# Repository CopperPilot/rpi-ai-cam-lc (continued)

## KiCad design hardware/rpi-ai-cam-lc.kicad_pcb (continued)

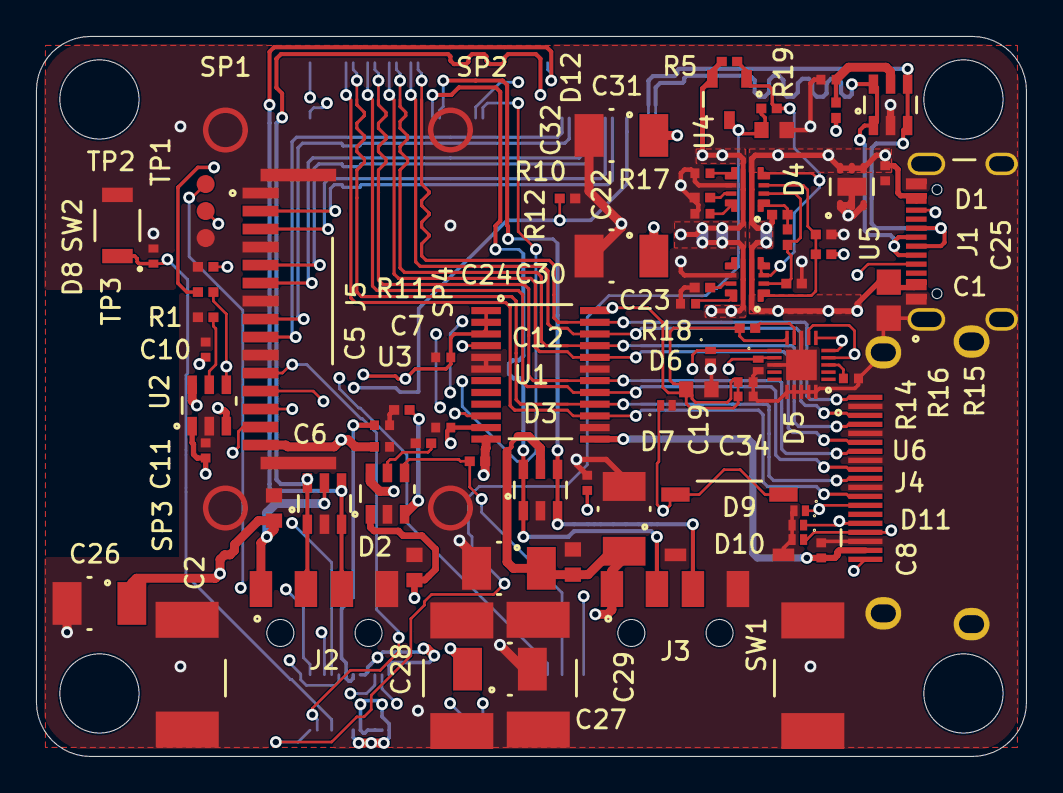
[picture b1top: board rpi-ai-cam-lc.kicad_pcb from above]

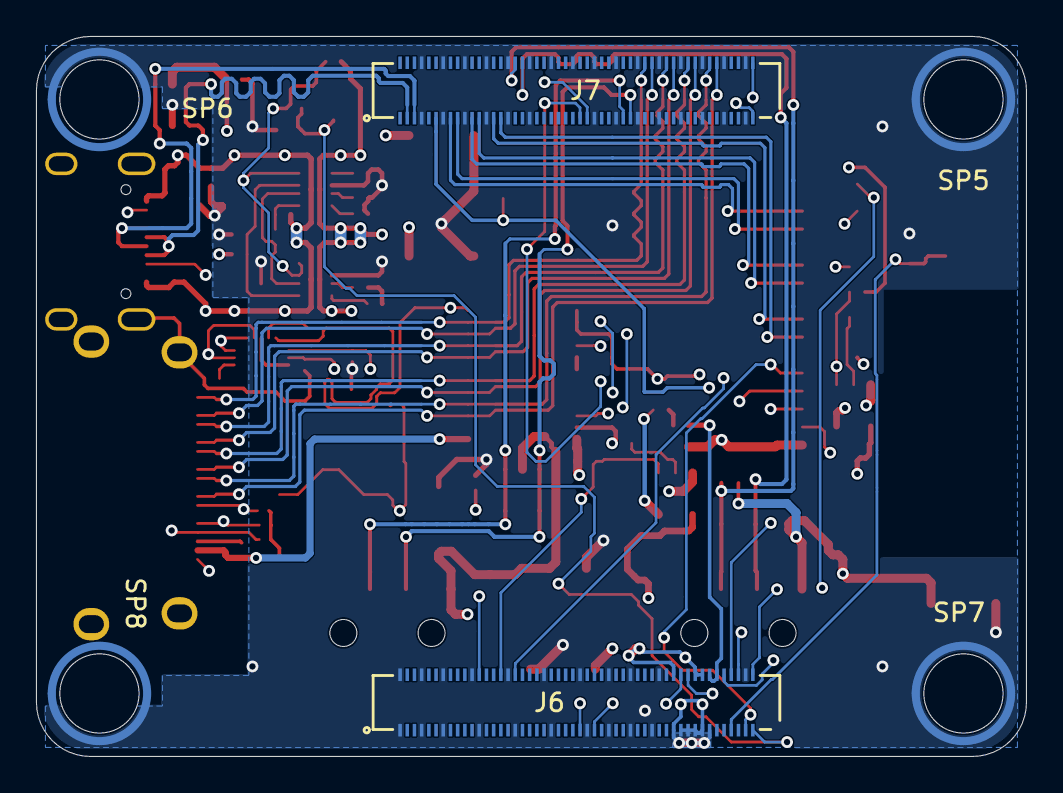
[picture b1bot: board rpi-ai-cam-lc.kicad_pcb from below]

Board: 6 copper layers, 55.0 x 40.0 mm, 88 parts (6 on the bottom side), 64 nets.

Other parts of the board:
H1, H2, H3, H4: MountingHole; MountingHole_4.4mm

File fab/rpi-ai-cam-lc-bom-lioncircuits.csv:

S.No,Manufacturing Part No,Designator,Quantity,Description (VALUE),Package (Case),Top/Bottom,Points (No. of Pins),Comments
1,CL21B225KBYNNWE,C1,1,"2.2uF 50V X7R 0805 MLCC on VBUS_IN (50V >= 1.79x D4 28.0V max clamp, unswitched cSink 2.3uF <= 10uF)",C0805,Top,2,Manufacturer: Samsung Electro-Mechanics
2,CL10A226MO7JZNC,"C2, C3, C19",3,"22uF 16V/10V X5R 0603 MLCC (Samsung CL10A226MO7JZNC / CL10A226MP8NUNE, J5 +3V3 camera bulk decoupling)",C0603,Top,2,Manufacturer: Samsung Electro-Mechanics
3,GRM155R71H104KE14D,"C4, C5, C6, C7, C20, C21, C25, C33",8,100nF 50V X7R 0402 MLCC,C0402,Top,2,Manufacturer: Murata
4,GRM155R61E105KE11J,"C8, C10, C11, C12, C34",5,1uF 25V X5R 0402 MLCC (U3 +5V input bypass),C0402,Top,2,Manufacturer: Murata
5,GRM188Z71E225KE43D,"C9, C32",2,"2.2uF 25V X7R 0603 RC blanking filter capacitor on PMIC_ENABLE (C_eff>=1.68uF at 5V, tau_fall>=10.7ms > 3.94ms t_ITIMER, tau_rise=2.42ms via R5+D12)",C0603,Top,2,Manufacturer: Murata
6,GRM155R71H472KA01D,"C22, C23, C24",3,"4.7nF 50V X7R 0402 dV/dt soft-start capacitor on U4 (SR=0.43V/ms, tR=11.7ms)",C0402,Top,2,Manufacturer: Murata
7,T520B107M010ATE070,"C26, C27, C28, C29, C30, C31",6,100uF 10V 70mOhm KO-CAP polymer tantalum bulk capacitor on J2 USB0_VBUS (1 of 2; 207.5uF effective with C27+C2 >= 120uF USB 2.0 C_PB),CAP-SMD_L3.5-W2.8,Top,2,Manufacturer: Kemet
8,USBLC6-2SC6,"D1, D2, D3",3,USBLC6-2SC6 - USB 2.0 ESD protection array,SOT-23-6_L2.9-W1.6-P0.95-LS2.8-BL,Top,6,Manufacturer: STMicroelectronics
9,TVS2200DRVR,D4,1,"TVS2200DRVR - 22V flat-clamp unidirectional surge TVS on J1 VBUS_IN (VRWM=22V, VBR=24.6-27.6V, VC=27.2V typ/27.7V max at 24A & 27.6V typ/28.0V max at 40A 8/20us <= 28V abs max, VF=-0.5V typ)",WSON-6_L2.0-W2.0-P0.65-TL-EP,Top,7,Manufacturer: Texas Instruments
10,TPD1E05U06DPYR,"D5, D6, D7, D9, D10, D11",6,TPD1E05U06DPYR - 5.5V unidirectional ESD TVS on protected system-side CC2 (downstream of U6 TPD6S300ARUKR 24V OVP FET) to GND,X1SON-2_L1.0-W0.6-P0.65-RD-1,Top,2,Manufacturer: Texas Instruments
11,PESD3V3S1BLYL,D8,1,PESD3V3S1BLYL - 3.3V bidirectional ESD TVS on SW2 nRPIBOOT,DFN1006-2L-BI,Top,2,Manufacturer: Nexperia
12,BAT54S,D12,1,"BAT54S - Dual series 30V 200mA Schottky diode (1->3 fast charge VBUS_AUXOFF->PMIC_ENABLE, 3->2 fast rail-collapse discharge PMIC_ENABLE->+5V)",SOT-23_L2.9-W1.3-P1.90-LS2.4-BR,Top,3,Manufacturer: Rectron
13,USB4105GFA,J1,1,USB4105-GF-A - GCT 16-pin USB 2.0 Type-C horizontal SMT receptacle,TYPE-C-SMD_SBC-160S1A-20-S412,Top,22,Manufacturer: GCT
14,629104190121,"J2, J3",2,629104190121 - Wurth WR-COM USB 2.0 Type-A horizontal SMT receptacle,USB-A-SMD_629104190121,Top,10,Manufacturer: Wurth Elektronik
15,10029449-111RLF,J4,1,10029449-111RLF - Amphenol full-size HDMI Type-A right-angle SMT receptacle,HDMI-SMD_10029449-001RLF,Top,23,Manufacturer: Amphenol ICC
16,SFW15R-1STE1LF,J5,1,SFW15R-1STE1LF - Amphenol 15-pin 1.0 mm right-angle bottom-contact ZIF FFC socket,CONN-SMD_15P-P0.50_SFW15R-1STE1LF,Top,17,Manufacturer: Amphenol Communications Solutions
17,10164227-1001A1RLF,"J6, J7",2,"10164227-1001A1RLF - Amphenol 100-pin 0.4 mm pitch mezzanine receptacle, 1.5 mm stack height (GPIO/Power pins 1-100 at B.Cu 25.0, 37.0, rot=180)",CONN-SMD_100P-P0.40_10164227-1001A1RLF,Bottom,100,Manufacturer: Amphenol Communications Solutions
18,RC0402FR-0743KL,"R1, R2, R16",3,"43k 1% 0402 bottom divider to GND on U5 EN/UVLO (with R15=100k sets UVLO_R=3.99V, UVLO_F=3.66V)",R0402,Top,2,Manufacturer: Yageo
19,RC0402FR-071K33L,"R5, R17, R18",3,"1.33k 1% 0402 current limit resistor for U4 (ILIM(typ)=2.50A, 5.0A combined <= J1 5.0A rating, ILIM(min)=2.28A)",R0402,Top,2,Manufacturer: Yageo
20,RC0402FR-0722KL,"R6, R7, R10, R11",4,22k 1% 0402 pull-down on USB_VBUS_EN (fast 4.4ms reset discharge with R11),R0402,Top,2,Manufacturer: Yageo
21,RC0402FR-07100KL,"R8, R9, R15, R20",4,100k 1% 0402 pull-up to VBUS_IN on U4 AUXOFF -> U5 EN/UVLO (per TI Figure 8-18),R0402,Top,2,Manufacturer: Yageo
22,RC0402FR-07390KL,R12,1,390k 1% 0402 top UVLO/OVLO divider resistor (>=350k per TI TPS25947 datasheet),R0402,Top,2,Manufacturer: Yageo
23,RC0402FR-0749K9L,R13,1,"49.9k 1% 0402 middle UVLO/OVLO divider resistor (UVLO_R=4.18V, OVLO_R=6.13V typ / 5.83V min > 5.50V vSafe5V)",R0402,Top,2,Manufacturer: Yageo
24,RC0402FR-07107KL,R14,1,"107k 1% 0402 bottom UVLO/OVLO divider resistor to GND (OVLO_R=6.13V typ / 5.83V min, OVLO_F=5.62V typ)",R0402,Top,2,Manufacturer: Yageo
25,RC0402FR-076K8L,R19,1,"6.8k 1% 0402 series RC filter resistor on VBUS_AUXOFF -> PMIC_ENABLE (tau_fall>=10.7ms > 3.94ms t_ITIMER with C32=2.2uF, V_LOW=0.37V < 0.40V)",R0402,Top,2,Manufacturer: Yageo
26,9774080243R,"SP1, SP2, SP3, SP4",4,9774080243R - Wurth WA-SMSI M2 internal thread 8.0 mm SMT steel spacer,SMD-1_BD4.4-D2.8,Top,1,Manufacturer: Wurth Elektronik
27,9774015960R,"SP5, SP6, SP7, SP8",4,9774015960R - 3.3mm ID 1.5mm SMT spacer,SMD_BD6.0-D4.2,Bottom,1,Manufacturer: Wurth Elektronik
28,PTS526SM15SMTR2LFS,SW1,1,PTS526SM15SMTR2LFS - SMT tactile switch,SW-SMD_4P-L5.2-W5.2-P3.70-LS6.4,Top,4,Manufacturer: C&K
29,B3U-1000P,SW2,1,B3U-1000P - Subminiature SMT tactile switch,KEY-SMD_B3U-1000PM,Top,2,Manufacturer: Omron
30,TPD12S016PWR,U1,1,TPD12S016PWR - TI HDMI companion IC,TSSOP-24_L7.8-W4.4-P0.65-LS6.4-BL,Top,24,Manufacturer: Texas Instruments
31,AP2553W6-7,"U2, U3",2,AP2553W6-7 - USB high-side power switch,SOT-26_L3.0-W1.6-P0.95-LS2.8-BL,Top,6,Manufacturer: Diodes Incorporated
32,TPS259470ARPWR,"U4, U5",2,"TPS259470ARPWR - TI 28mOhm 5.5A ideal-diode OVP eFuse (primary inrush channel, parallel R_ON=14.1mOhm)",VQFN-10_L2.0-W2.0-P0.45-TL,Top,10,Manufacturer: Texas Instruments
33,TPD6S300ARUKR,U6,1,TPD6S300ARUKR - TI 24V-tolerant USB Type-C CC1/CC2 series OVP FETs + IEC 61000-4-2 ESD protection + dead-battery Rd,WQFN-20_L3.0-W3.0-P0.40-TL-EP1.7,Top,21,Manufacturer: Texas Instruments

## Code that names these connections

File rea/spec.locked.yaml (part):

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  must_match:
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    - {id: F2, name: power button, kind: button, view: front, center_mm: [40.5, 29.6], size_mm: [4.5, 4.5], implement: pcb+case, source: photo, confidence: high, notes: "Momentary power button over SW1 on PWR_BUT at board (38.5, 27.6), moved below the y=7.7..23.7 mm 16 mm FFC U-turn band"}
    - {id: F3, name: boot pinhole, kind: button, view: front, center_mm: [6.5, 12.5], size_mm: [2.0, 2.0], implement: pcb+case, source: photo, confidence: high, notes: "Paperclip pinhole over SW2 on nRPIBOOT at board (4.5, 10.5)"}
    - {id: F4, name: USB-C power and flashing port, kind: port, view: right, center_mm: [13.5, 16.75], size_mm: [9.5, 3.8], implement: pcb+case, source: photo, confidence: high, notes: "Right-edge opening for J1 GCT USB4105-GF-A at board (51.5, 11.5)"}
    - {id: F5, name: HDMI port, kind: port, view: right, center_mm: [27.0, 15.3], size_mm: [15.5, 6.2], implement: pcb+case, source: photo, confidence: high, notes: "Right-edge opening for J4 Amphenol 10029449-111RLF at board (49.0, 25.0)"}
    - {id: F6, name: USB 2.0 Type-A host port 0, kind: port, view: bottom, center_mm: [18.0, 14.85], size_mm: [14.8, 7.2], implement: pcb+case, source: photo, confidence: high, notes: "Bottom-edge opening for J2 Wurth 629104190121 at board (16.0, 34.3)"}
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    - ["J5.6", "MIPI0_D1_P"]
    - ["J5.8", "MIPI0_C_N"]
    - ["J5.9", "MIPI0_C_P"]
    - ["J5.11", "CAM_GPIO0"]
    - ["J5.12", "CAM_GPIO1"]
    - ["J5.13", "SCL0"]
    - ["J5.14", "SDA0"]
    - ["J5.15", "+3V3"]
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      - {layer: dielectric_1, kind: prepreg, material: "7628", thickness_mm: 0.19, epsilon_r: 4.69}
      - {layer: In1.Cu, role: gnd_plane, copper_mm: 0.0175, net: GND, notes: "L2 unbroken 0.5 oz (0.0175 mm) solid GND reference plane for F.Cu high-speed pairs and In2.Cu signals"}
      - {layer: dielectric_2, kind: core, material: "GDM-140", thickness_mm: 0.45, epsilon_r: 4.5, notes: "0.450 mm GDM-140 core (Tg 140, Dk=4.5)"}
      - {layer: In2.Cu, role: signal, copper_mm: 0.0175, notes: "L3 inner 0.5 oz (0.0175 mm) signal layer for slow/control nets and >=0.80 mm wide power feeds (USB0_VBUS, USB1_VBUS, +3V3 keeping dT <= 10 C on 0.5 oz copper)"}
      - {layer: dielectric_3, kind: prepreg, material: "7628", thickness_mm: 0.19, epsilon_r: 4.69}
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      - {layer: dielectric_4, kind: core, material: "GDM-140", thickness_mm: 0.45, epsilon_r: 4.5, notes: "0.450 mm GDM-140 core (Tg 140, Dk=4.5)"}
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  - {refs: [R14], role: uvlo_ovlo_bot, mpn: RC0402FR-07107KL, lcsc: C138070, footprint: "lcsc:R0402", description: "Yageo 107 kOhm 1% 0402 bottom UVLO/OVLO divider resistor (setting UVLO_R=4.18 V, OVLO_R=6.13 V typ / 5.83 V min, OVLO_F=5.62 V typ / 5.33 V min)"}
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  - {refs: [C1], role: vbus_in_bypass_2u2_50v, mpn: CL21B225KBYNNWE, lcsc: C6534398, footprint: "lcsc:C0805", description: "Samsung 2.2 uF 50V X7R 0805 MLCC on VBUS_IN (50V rating >= 1.79x D4 TVS2200DRVR 28.0V max clamping voltage, keeping unswitched cSink at 2.3 uF nominal <= 10 uF)"}
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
